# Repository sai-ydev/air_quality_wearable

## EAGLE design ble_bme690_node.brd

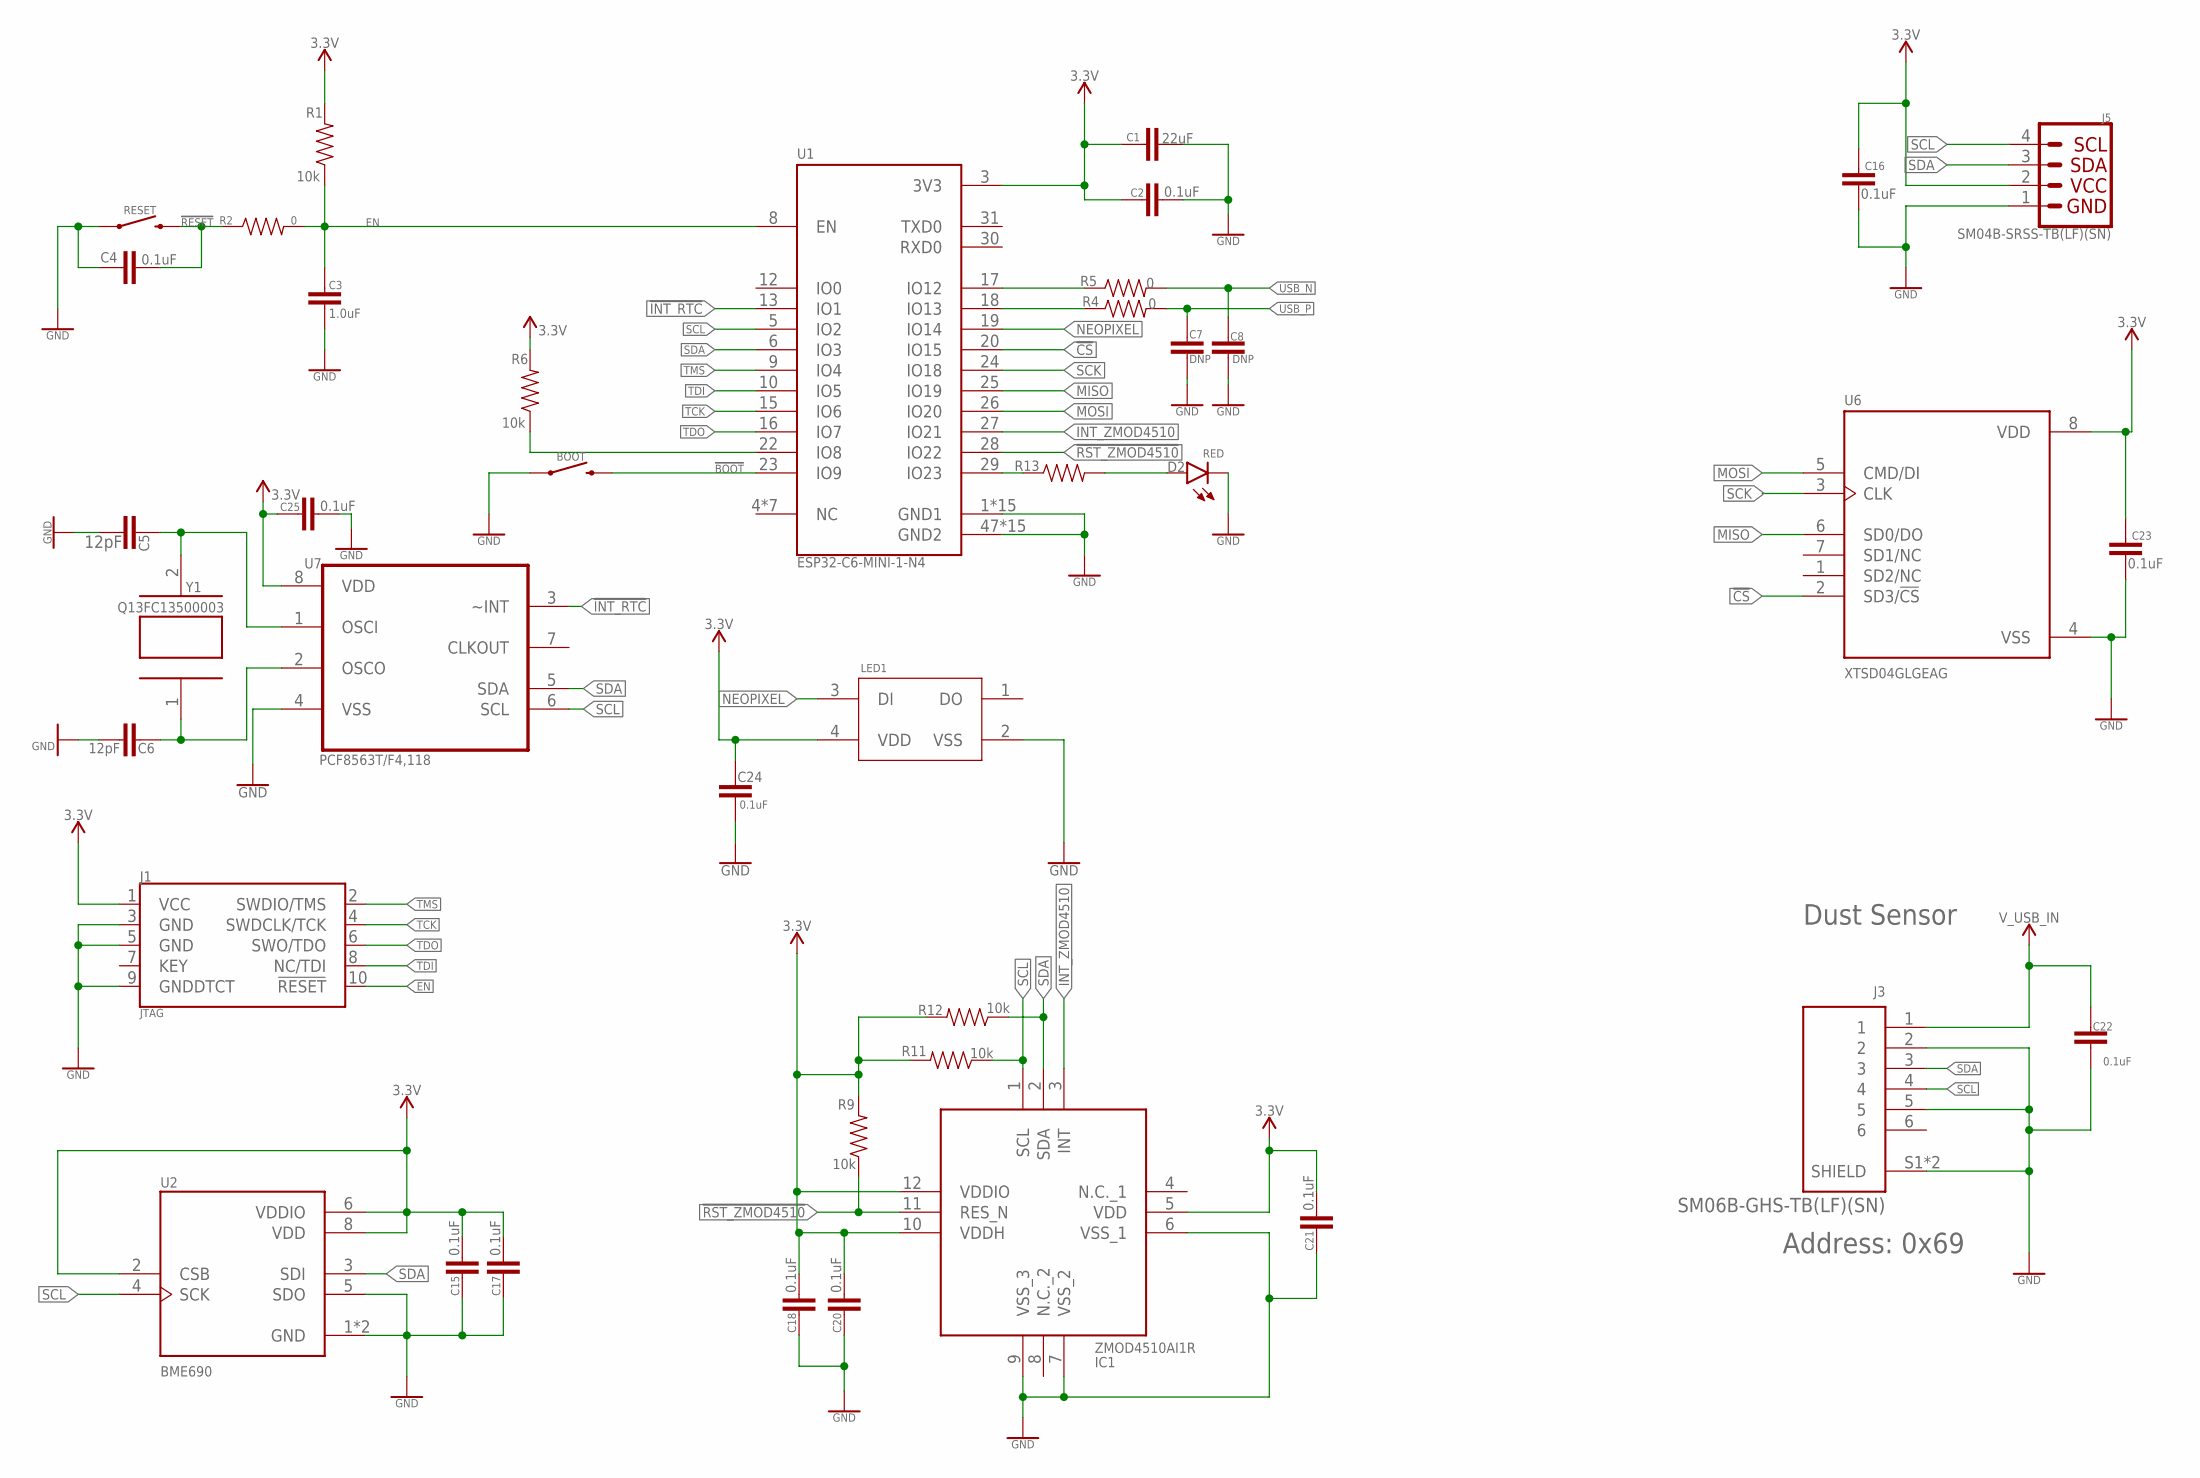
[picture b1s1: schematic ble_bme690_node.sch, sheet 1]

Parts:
BOOT: MOMENTARY-SWITCH-SPST-SMD-4.6X2.8MM; TACTILE_SWITCH_SMD_4.6X2.8MM
C1: 22uF; 0603
C2, C4, C15, C16, C17, C18, C20, C21, C22, C23, C24, C25: 0.1uF; 0402
C3: 1.0uF; 0402
C5, C6: 12pF; 0402
C7, C8: DNP; 0402
D2: RED; LED-0603
IC1: ZMOD4510AI1R
J1: JTAG; 2X5-SMD-UNSHROUDED
J3: SM06B-GHS-TB(LF)(SN); JST_SM06B-GHS-TB(LF)(SN)
J5: SM04B-SRSS-TB(LF)(SN); 1X04_1MM_RA
LED1: WS2812B-2020
R1, R6, R9, R11, R12: 10k; 0402
R2, R4, R5: 0; 0402
R13: 100OHM; 0402
RESET: MOMENTARY-SWITCH-SPST-SMD-4.6X2.8MM; TACTILE_SWITCH_SMD_4.6X2.8MM
U1: ESP32-C6-MINI-1-N4; XCVR_ESP32-C6-MINI-1-N4
U2: BME690; IC_BME688
U6: XTSD04GLGEAG; SON127P600X800X95-8N
U7: PCF8563T/F4,118; SOIC127P600X175-8N
Y1: Q13FC13500003; XTAL_FC-135_32.7680KA-A0

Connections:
3.3V: C1.1, C2.1, C15.2, C16.2, C17.2, C18.2, C20.2, C21.2, C23.2, C24.1, C25.1, IC1.5 (VDD), IC1.10 (VDDH), IC1.12 (VDDIO), J1.1 (VCC), J5.2, LED1.4 (VDD), R1.2, R6.2, R9.2, R11.2, R12.2, U1.3 (3V3), U2.2 (CSB), U2.6 (VDDIO), U2.8 (VDD), U6.8 (VDD), U7.8 (VDD); also elsewhere on the board
!BOOT: BOOT.3 (2), BOOT.4 (2), U1.23 (IO9)
!CS: U1.20 (IO15), U6.2 (SD3/!CS)
!INT_RTC: U1.13 (IO1), U7.3 (~INT)
!RESET: C4.2, R2.1, RESET.3 (2), RESET.4 (2)
!RST_ZMOD4510: IC1.11 (RES_N), R9.1, U1.28 (IO22)
EN: C3.2, J1.10 (!RESET), R1.1, R2.2, U1.8 (EN)
GND: BOOT.1, BOOT.2 (1), C1.2, C2.2, C3.1, C4.1, C5.2, C6.2, C7.2, C8.2, C15.1, C16.1, C17.1, C18.1, C20.1, C21.1, C22.2, C23.1, C24.2, C25.2, D2.C, IC1.6 (VSS_1), IC1.7 (VSS_2), IC1.9 (VSS_3), J1.3 (GND), J1.5 (GND), J1.9 (GNDDTCT), J3.2, J3.5, J3.S1 (SHIELD), J3.S2 (SHIELD), J5.1, LED1.2 (VSS), RESET.1, RESET.2 (1), U1.1 (GND1), U1.2 (GND1), U1.11 (GND1), U1.14 (GND1), U1.36 (GND1), U1.37 (GND1), U1.38 (GND1), U1.39 (GND1), U1.40 (GND1), U1.41 (GND1), U1.42 (GND1), U1.43 (GND1), U1.44 (GND1), U1.45 (GND1), U1.46 (GND1), U1.47 (GND2), U1.48 (GND2), U1.49_1 (GND2), U1.49_2 (GND2), U1.49_3 (GND2), U1.49_4 (GND2), U1.49_5 (GND2), U1.49_6 (GND2), U1.49_7 (GND2), U1.49_8 (GND2), U1.49_9 (GND2), U1.50 (GND2), U1.51 (GND2), U1.52 (GND2), U1.53 (GND2), U2.1 (GND), U2.5 (SDO), U2.7 (GND), U6.4 (VSS), U7.4 (VSS); also elsewhere on the board
INT_ZMOD4510: IC1.3 (INT), U1.27 (IO21)
MISO: U1.25 (IO19), U6.6 (SD0/DO)
MOSI: U1.26 (IO20), U6.5 (CMD/DI)
unnamed: R5.1, U1.17 (IO12)
unnamed: R4.1, U1.18 (IO13)
unnamed: R6.1, U1.22 (IO8)
unnamed: C5.1, U7.1 (OSCI), Y1.2
unnamed: R13.1, U1.29 (IO23)
unnamed: D2.A, R13.2
NEOPIXEL: LED1.3 (DI), U1.19 (IO14)
RTC_IN: C6.1, U7.2 (OSCO), Y1.1
SCK: U1.24 (IO18), U6.3 (CLK)
SCL: IC1.1 (SCL), J3.4, J5.4, R11.1, U1.5 (IO2), U2.4 (SCK), U7.6 (SCL)
SDA: IC1.2 (SDA), J3.3, J5.3, R12.1, U1.6 (IO3), U2.3 (SDI), U7.5 (SDA)
TCK: J1.4 (SWDCLK/TCK), U1.15 (IO6)
TDI: J1.8 (NC/TDI), U1.10 (IO5)
TDO: J1.6 (SWO/TDO), U1.16 (IO7)
TMS: J1.2 (SWDIO/TMS), U1.9 (IO4)
USB_N: C8.1, R5.2; also elsewhere on the board
USB_P: C7.1, R4.2; also elsewhere on the board
V_USB_2: C22.1, J3.1; also elsewhere on the board

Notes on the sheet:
Dust Sensor
Address: 0x69

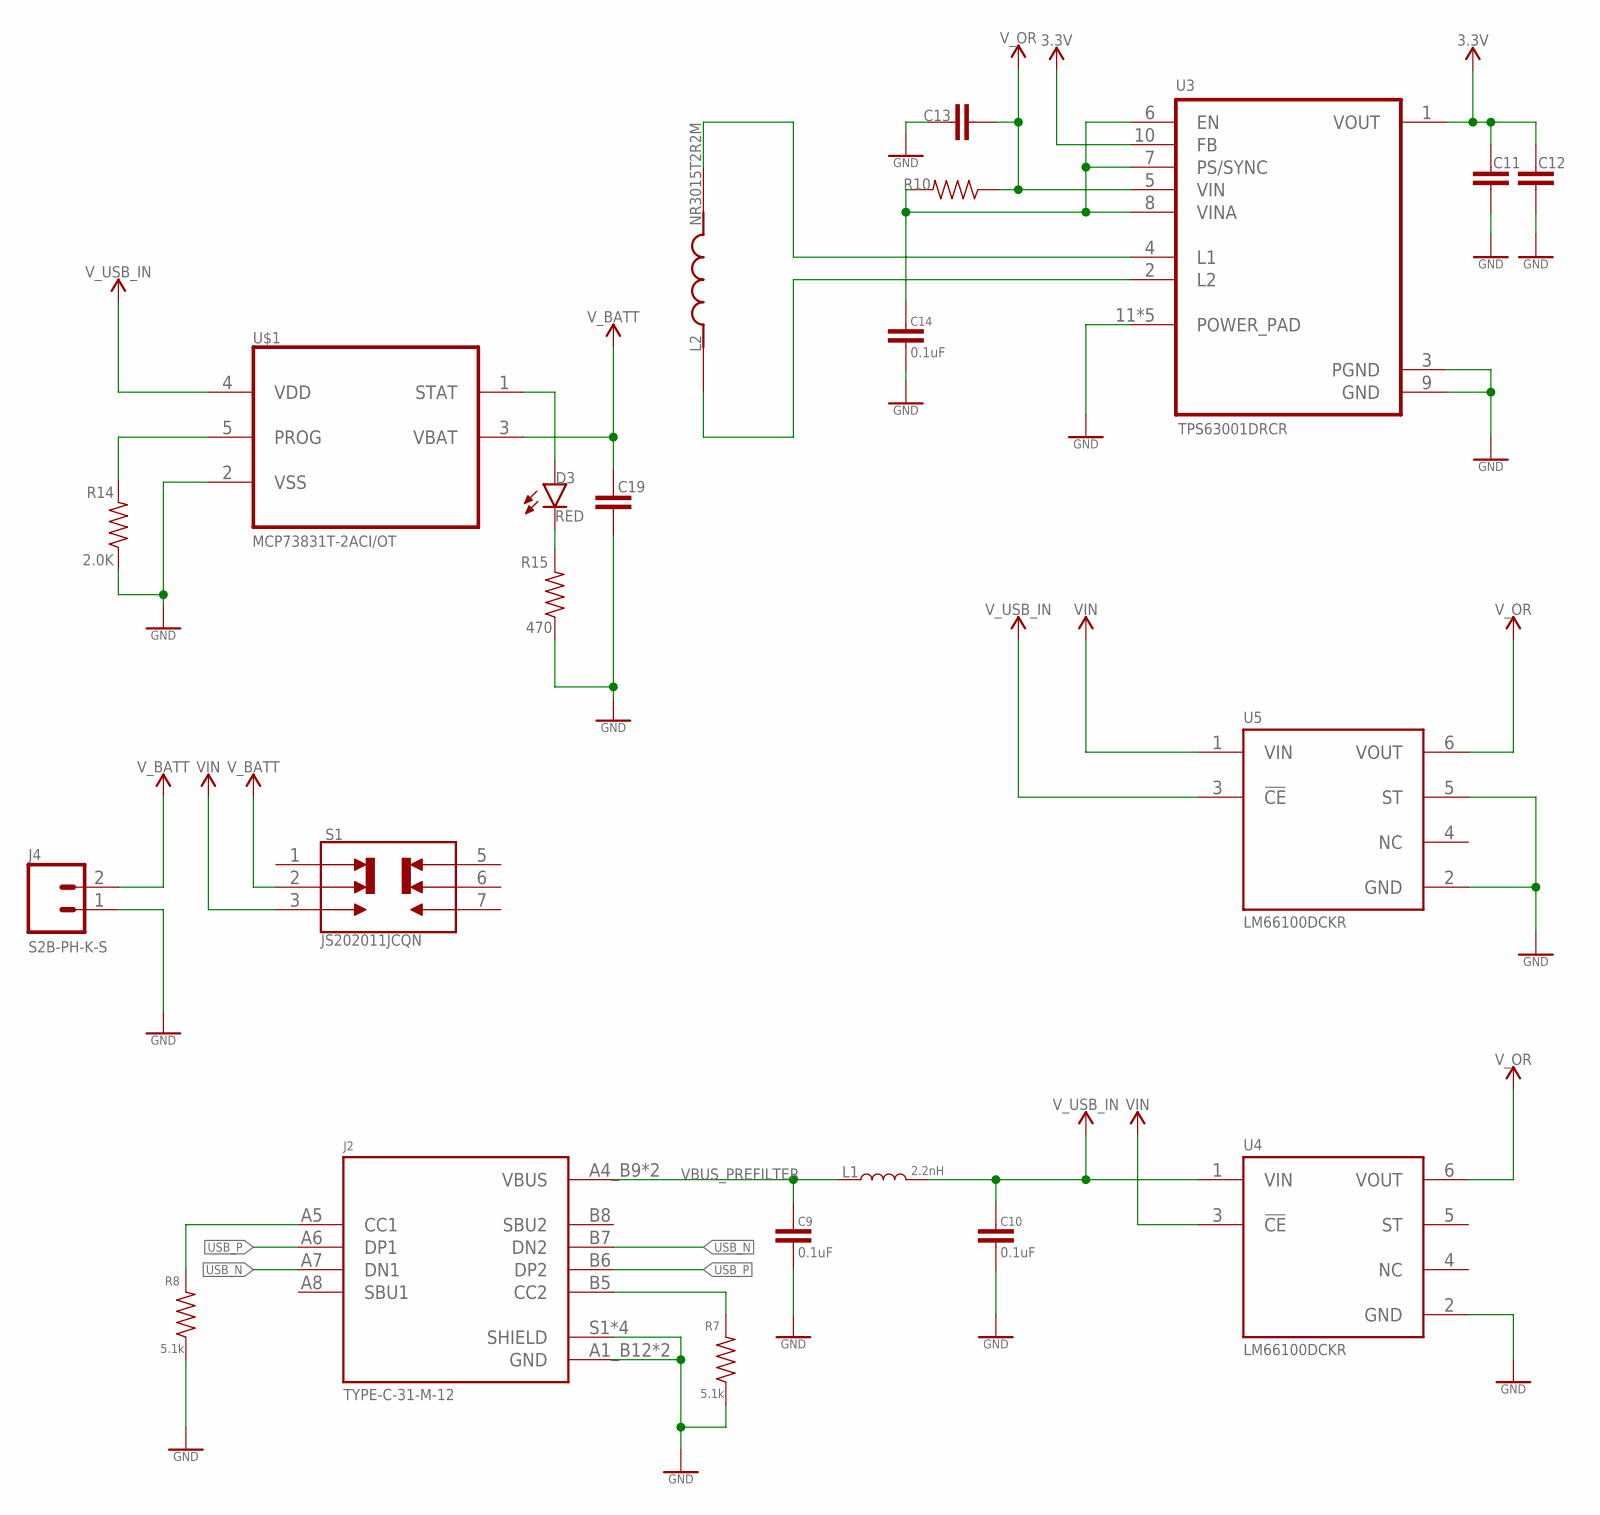
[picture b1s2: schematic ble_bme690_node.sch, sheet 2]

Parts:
C9, C10, C14: 0.1uF; 0402
C11, C12, C13: 10UF0402; 0402
C19: 4.7UF0402; 0402
D3: RED; LED-0603
J2: TYPE-C-31-M-12; HRO_TYPE-C-31-M-12
J4: S2B-PH-K-S; JST-2-PTH-NS
L1: 2.2nH; 0603
L2: NR3015T2R2M; IND_NR3015T2R2M
R7, R8: 5.1k; 0402
R10: 100OHM; 0402
R14: 2.0K; 0402
R15: 470; 0402
S1: JS202011JCQN; SW_JS202011JCQN
U3: TPS63001DRCR; VREG_V62/16624-01YE
U4, U5: LM66100DCKR; SOT65P210X110-6N
U$1: MCP73831T-2ACI/OT; SOT95P280X145-5N

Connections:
3.3V: C11.1, C12.1, U3.1 (VOUT), U3.10 (FB); also elsewhere on the board
GND: C9.1, C10.1, C11.2, C12.2, C13.1, C14.1, C19.2, J2.A1_B12 (GND), J2.B1_A12 (GND), J2.S1 (SHIELD), J2.S2 (SHIELD), J2.S3 (SHIELD), J2.S4 (SHIELD), J4.1, R7.1, R8.1, R14.1, R15.1, U3.3 (PGND), U3.9 (GND), U3.11 (POWER_PAD), U3.12 (POWER_PAD), U3.13 (POWER_PAD), U3.14 (POWER_PAD), U3.15 (POWER_PAD), U4.2 (GND), U5.2 (GND), U5.5 (ST), U$1.2 (VSS); also elsewhere on the board
unnamed: J2.B5 (CC2), R7.2
unnamed: J2.A5 (CC1), R8.2
unnamed: L2.1, U3.2 (L2)
unnamed: L2.2, U3.4 (L1)
unnamed: C14.2, R10.2, U3.6 (EN), U3.7 (PS/SYNC), U3.8 (VINA)
unnamed: R14.2, U$1.5 (PROG)
unnamed: D3.A, U$1.1 (STAT)
unnamed: D3.C, R15.2
USB_N: J2.A7 (DN1), J2.B7 (DN2); also elsewhere on the board
USB_P: J2.A6 (DP1), J2.B6 (DP2); also elsewhere on the board
VBUS_PREFILTER: C9.2, J2.A4_B9 (VBUS), J2.B4_A9 (VBUS), L1.1
VIN: S1.3, U4.3 (!CE), U5.1 (VIN)
VREF1: C13.2, R10.1, U3.5 (VIN), U4.6 (VOUT), U5.6 (VOUT)
V_BATT: C19.1, J4.2, S1.2, U$1.3 (VBAT)
V_USB_2: C10.2, L1.2, U4.1 (VIN), U5.3 (!CE), U$1.4 (VDD); also elsewhere on the board

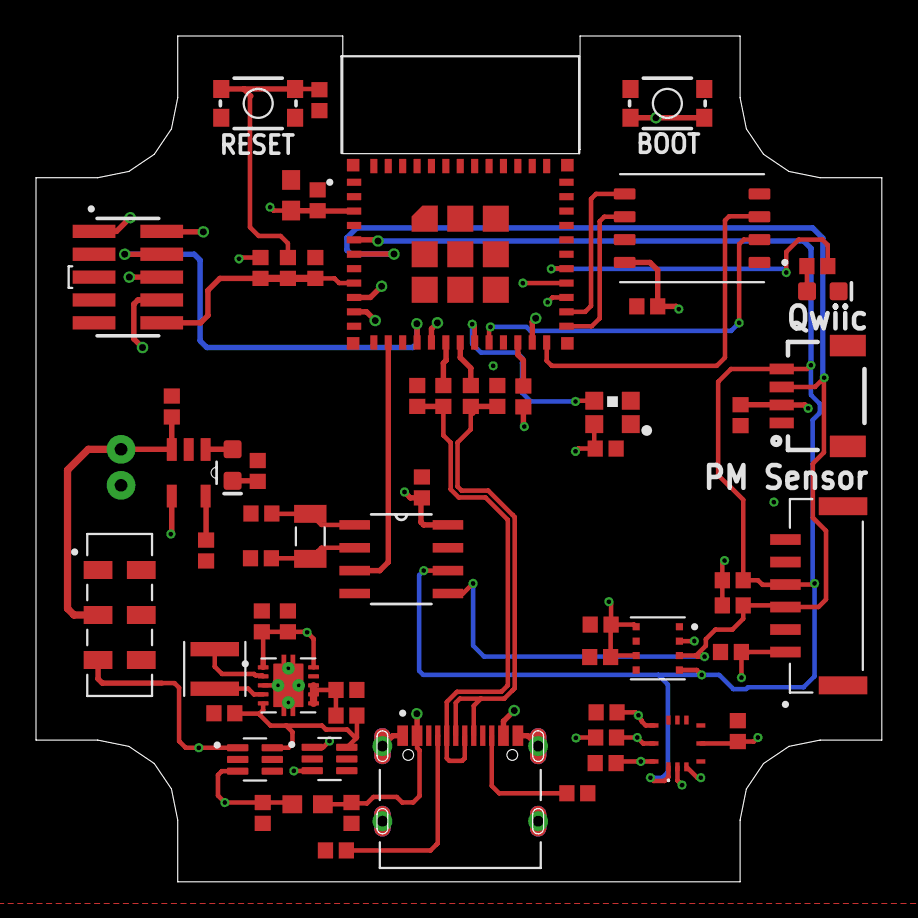
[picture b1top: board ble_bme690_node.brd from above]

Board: 4 copper layers, 47.0 x 47.0 mm, 62 parts (1 on the bottom side), 41 nets.

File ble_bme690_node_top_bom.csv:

Comment,Designator,Footprint,LCSC Part #
0,R2 R4 R5,0402,
0.1uF,C2 C4 C9 C10 C14 C15 C16 C17 C18 C20 C21 C22 C23 C24 C25,0402,
1.0uF,C3,0402,
2.0K,R14,0402,
2.2nH,L1,0603,
4.7UF0402,C19,0402,
5.1k,R7 R8,0402,
10UF0402,C11 C12 C13,0402,
10k,R1 R6 R9 R11 R12,0402,
12pF,C5 C6,0402,
22uF,C1,0603,
100OHM,R10 R13,0402,
470,R15,0402,
BME690,U2,IC_BME688,
DNP,C7 C8,0402,
ESP32-C6-MINI-1-N4,U1,XCVR_ESP32-C6-MINI-1-N4,
JS202011JCQN,S1,SW_JS202011JCQN,
JTAG,J1,2X5-SMD-UNSHROUDED,
LM66100DCKR,U4 U5,SOT65P210X110-6N,
MCP73831T-2ACI/OT,U$1,SOT95P280X145-5N,
MOMENTARY-SWITCH-SPST-SMD-4.6X2.8MM,BOOT RESET,TACTILE_SWITCH_SMD_4.6X2.8MM,
NR3015T2R2M,L2,IND_NR3015T2R2M,
PCF8563T/F4 118,U7,SOIC127P600X175-8N,
Q13FC13500003,Y1,XTAL_FC-135_32.7680KA-A0,
RED,D2 D3,LED-0603,
SM04B-SRSS-TB(LF)(SN),J5,1X04_1MM_RA,
SM06B-GHS-TB(LF)(SN),J3,JST_SM06B-GHS-TB(LF)(SN),
TPS63001DRCR,U3,VREG_V62/16624-01YE,
TYPE-C-31-M-12,J2,HRO_TYPE-C-31-M-12,
WS2812B-2020,LED1,WS2812B-2020,
XTSD04GLGEAG,U6,SON127P600X800X95-8N,
ZMOD4510AI1R,IC1,ZMOD4510AI1R,

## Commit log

2025-02-23 Created files from MAX30210 project
2025-02-24 Completed design files
2026-01-02 ESP32-IDF design files
2026-01-05 Completed BME690 drivers
2026-01-11 ZMOD4510 drivers
2026-03-05 code checked in
2026-03-14 Trained model
2026-05-14 Design files check-in
2026-05-27 Kicad schematic - daily backup.

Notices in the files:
parts and their libraries:
SparkFun-Switches: Licensing: Creative Commons ShareAlike 4.0 International - https://creativecommons.org/licenses/by-sa/4.0
